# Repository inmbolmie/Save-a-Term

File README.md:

# Save-a-Term

Hardware for an IBM 5251 and 3278 reverse keyboard adapter to use a regular PS/2 keyboard with the original terminals. Based on my TMK controller fork (https://github.com/inmbolmie/ps2_to_4704_converter)

## Introduction

You got a pretty vintage 5251 or 3278 terminal but it lacks the original keyboard. The original keyboards are very expensive and sought-after items that can easily go for thousands of dollars. This adapter tries to solve that problem giving a way to use a cheap standard PS/2-like keyboard with the original terminals.

The adapter emulates the clicker functionality of the original keyboards using a buzzer to give audible feedback while typing.

The adapter will also auto-detect the terminal type (5251 or 3278) and use the correct scancode set and signal polarities for the connected terminal.

If you like it, want an adapter or PCB, or need any information not covered here you can drop me an email to the address:  inmbolmie [AT] gmail [DOT] com

## Compatibility

This converter is only compatible with original IBM 5251 and 3278 terminals.

- The original IBM 5251 terminal keyboard has a DB25 female connector
- The original IBM 3278 terminal keyboard has a DB25 male connector

If not totally sure, check the voltages accross your terminal connector pins before plugging it to the adapter, here you have the expected 5251 and 3278 keyboard pinouts:

__This adapter is not compatible with other similar IBM connectors like 3277, 5291 or Displaywriter, so do not try it with those.__

This is not an adapter to plug an original 5251/3278 keyboard to a modern PC and won't ever work like that, so don't ask.

Pinouts are fully incompatible so a different connector is provided for each terminal type. Moreover, __it is dangerous to connect the terminal to the wrong connector as pretty weird voltages will be misplaced accross the connector (+8.5V, +5V, -5V) so you can fry the converter and/or terminal doing that, so be warned.__

This controller do not pretend to be universal in the sense some keyboards could be not compatible, but to provide a reasonable selection of cheap keyboards readily available. I have tested the converter using:

* Regular IBM model M
* IBM PC (XT)
* IBM AT (Model F)
* IBM terminal keyboards (M and F)
* Several PS/2 compatible keyboards

As said, it is not guaranteed that a particular keyboard will work, but there is a more than reasonable chance that any keyboard compatible with those metioned will work.

This converter is NOT compatible with USB keyboards. The pro-micro USB connector is provided only as way to update the controller's firmware.

## Usage

The adapter will get power from the terminal connector, so no external power is needed.

For the connection to the terminal you have to use a __male-to-female straight DB-25 cable__

To use the adapter you simply have to plug __ONE keyboard__ to one of the 4 available ports (RJ45, DIN5-240º, DIN5-180º, PS/2) and __the terminal to the right DB-25 connector (female for 5251 and male for 3278)__. The terminal type and connector gender is also clearly marked on the PCB silkscreen. Check that your cable is really straight, pin 1 goes to pin 1, pin 2 goes to pin 2, etc. __It is of the utmost importance not to mix genders or plug the terminal to the wrong connector__, as pretty high voltages are involved on the connectors (+8.5V, +5V. -5V) and the pinouts are incompatible. If you get it wrong you will damage the adapted and/or terminal. __You cannot get it wrong if you stick to only using a male-to-female straight DB25 cable__, as there is no way of plugging it on a wrong configuration.

The adapter will auto-detect the terminal type (5251 or 3278) and use the correct scancode set and signal polarities for the connected terminal.

The buzzer volume can be adjusted using the on-board potentiometer. On the spririt of the original keyboards, the buzzer can be totally silenced only from the terminal (like the clicker on the original keyboards).

The included DIP switches allow to configure a 4-bit keyboard-id for the terminal. The keyboard-id is exclusively used by the terminal and do not modify the adapter operation.

## Layouts

The layouts are designed to replicate the original keyboard functionality. They are not configurable.

### 5251 using a codeset 1 keyboard (XT)

This is the recommended layout for 5251, as it is exactly the same as the original keyboard

### 5251 using a codeset 2 or 3 keyboard (AT/PS2/Terminal)

Offers the same functionality as the original keyboard, placing keys on similar positions.

### 3278 using a codeset 2 or 3 keyboard (AT/PS2/Terminal)

This is the recommended layout for 3278, offers extra fuctionality and layout loosely based on 122-key 3270-compatible terminals

### 3278 using a codeset 1 keyboard (XT)

Do not use it as some keys will be on weird places, offered only for compatibility reasons.

## Kicad files

### Schematics

The design is based on the pro-micro version of TMK adding parallel protocol compatibility.

### PCB

## Case

I provide the STL files for a 3D-printed case (case and lid). The case is assembled using 4 M3x10mm tapered head screws.

## Fabrication

You can order the PCB's directly from JLCPCB using the provided gerber, bom, and cpl files on the `pcb` directory. You can easily generate files for other fabricators from the Kicad project files.

## Assembly

For the assembly be sure you get the correct gender for DB-25 connectors respecting what is indicated on the silkscreen legends.

You have to use a 5V-16Mhz Arduino pro-micro genuine or compatible microcontroller.

The 7805 regulator can be a regular 7805 or (better) a DC-to-DC pin compatible replacement like a Traco TSR 1-2450E. A 7805 is used to power the board from the 8.5V rail instead of using the +5V rail directly because I found the latter unstable and sometimes providing insufficient voltage to power the controller reliably.

## Programming

You have to use my fork of TMK https://github.com/inmbolmie/ps2_to_4704_converter

`git clone https://github.com/inmbolmie/ps2_to_4704_converter.git`

Go to the `converter/ibmpc_ibm5251` directory and generate the firmware file executing:

`cd ps2_to_4704_converter/converter/ibmpc_ibm5251/`

`make -f Makefile.atmega32u4`

To program the controller, connect it to an USB port on your computer, making sure no terminal is connected to the adapter in case the controller is already soldered on the board. Then push the RESET button on the board and execute on your computer:

`avrdude -p m32U4 -P /dev/ttyACM0 -c avr109 -U flash:w:ibmpc_ibm5251_atmega32u4.hex`

 Where `ibmpc_ibm5251_atmega32u4.hex` is the name of the generated firmware file.

The device name `ttyACM0` could have to be changed to whatever device name your computer assigns to your controller.

__Do not plug the USB port while a terminal is connected to the adapter__

You will need to have the tools needed to build TMK, follow the general instrucions from the TMK code to configure your build environment.

After successful programming you will get output like this:

    Connecting to programmer: .
    Found programmer: Id = "CATERIN"; type = S
        Software Version = 1.0; No Hardware Version given.
    Programmer supports auto addr increment.
    Programmer supports buffered memory access with buffersize=128 bytes.

    Programmer supports the following devices:
        Device code: 0x44

    avrdude: AVR device initialized and ready to accept instructions

    Reading | ################################################## | 100% 0.00s

    avrdude: Device signature = 0x1e9587 (probably m32u4)
    avrdude: NOTE: "flash" memory has been specified, an erase cycle will be performed
             To disable this feature, specify the -D option.
    avrdude: erasing chip
    avrdude: reading input file "ibmpc_ibm5251_atmega32u4.hex"
    avrdude: input file ibmpc_ibm5251_atmega32u4.hex auto detected as Intel Hex
    avrdude: writing flash (27136 bytes):

    Writing | ################################################## | 100% 1.69s

    avrdude: 27136 bytes of flash written
    avrdude: verifying flash memory against ibmpc_ibm5251_atmega32u4.hex:
    avrdude: load data flash data from input file ibmpc_ibm5251_atmega32u4.hex:
    avrdude: input file ibmpc_ibm5251_atmega32u4.hex auto detected as Intel Hex
    avrdude: input file ibmpc_ibm5251_atmega32u4.hex contains 27136 bytes
    avrdude: reading on-chip flash data:

    Reading | ################################################## | 100% 0.17s

    avrdude: verifying ...
    avrdude: 27136 bytes of flash verified

    avrdude: safemode: Fuses OK (E:CB, H:D8, L:FF)

    avrdude done.  Thank you.

Now your controller is ready to be used.

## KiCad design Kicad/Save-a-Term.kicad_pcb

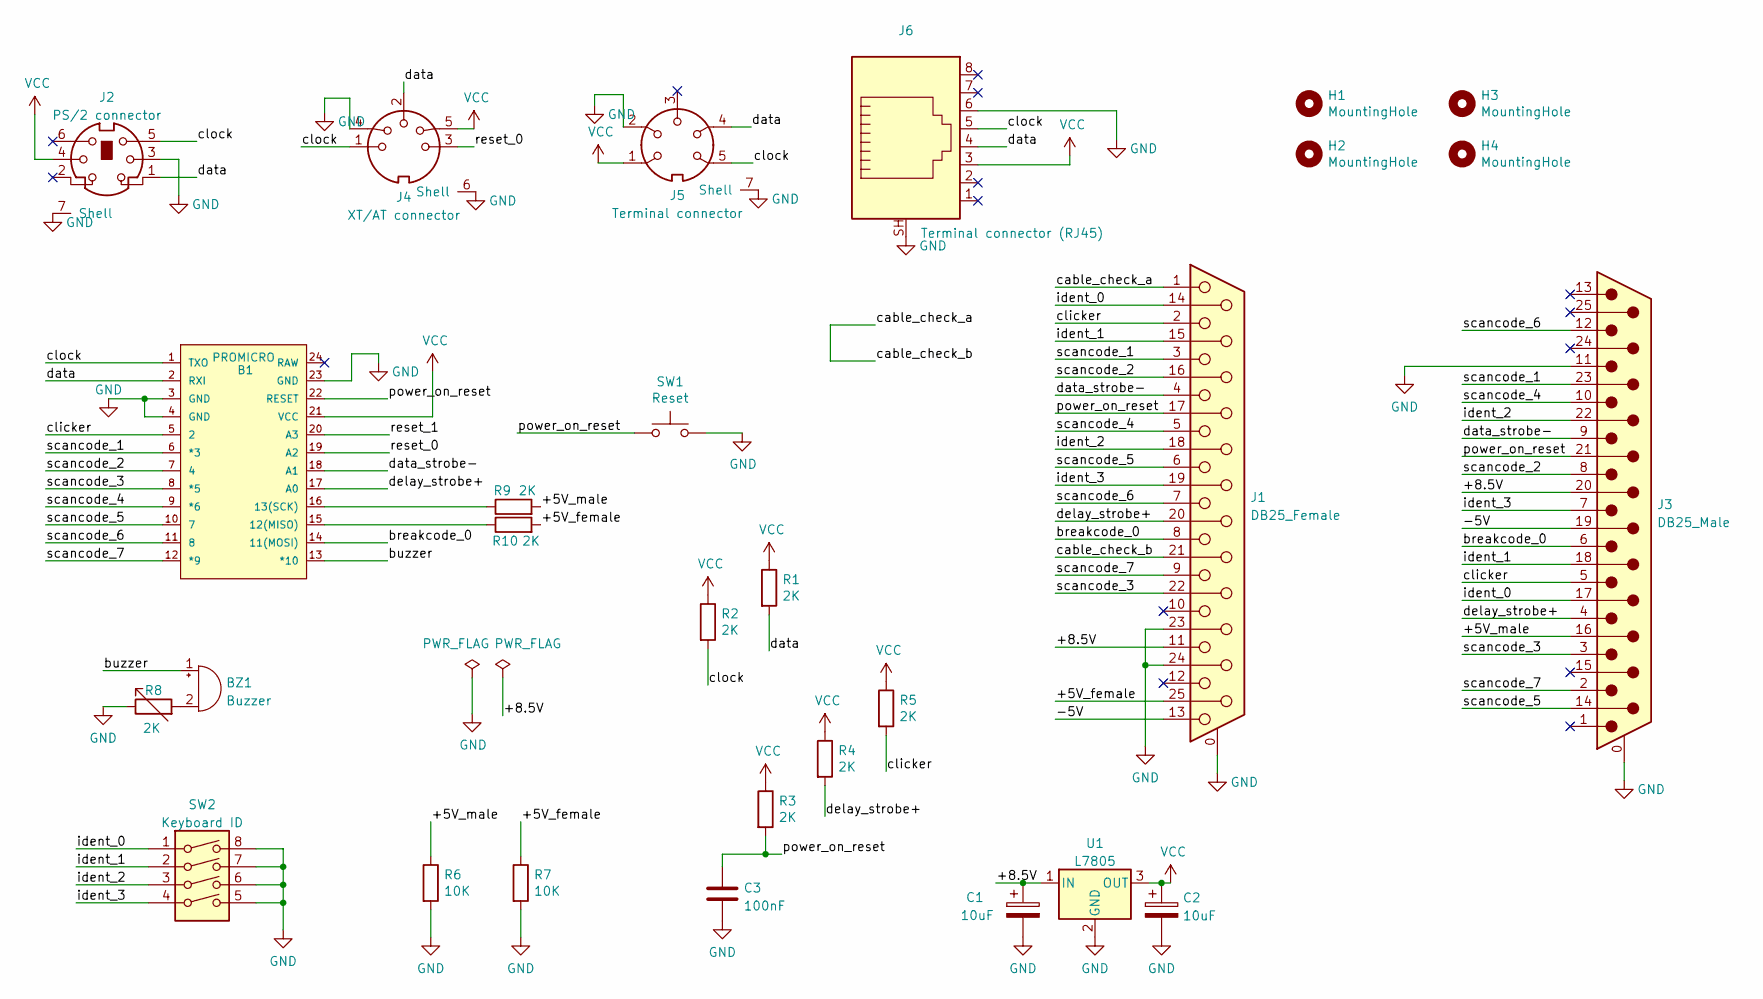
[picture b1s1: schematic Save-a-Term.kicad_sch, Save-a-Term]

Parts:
B1: PROMICRO; SPARKFUN_PRO_MICRO
BZ1: Buzzer; Buzzer_12x9.5RM7.6
C1, C2: 10uF; C_1206_3216Metric; LCSC C13585
C3: 100nF; C_0603_1608Metric; LCSC C14663
H1, H2, H3, H4: MountingHole; MountingHole_3.2mm_M3
J1: DB25_Female; DSUB-25_Female_Horizontal_P2.77x2.84mm_EdgePinOffset7.70mm_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
J2: PS/2 connector; Connector_Mini-DIN_Female_6Pin_2rows
J3: DB25_Male; DSUB-25_Male_Horizontal_P2.77x2.84mm_EdgePinOffset7.70mm_Ho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
J4: XT/AT connector; DIN-5
J5: Terminal connector; DIN-6
J6: Terminal connector (RJ45); RJ45_Ninigi_GE
R1, R2, R3, R4, R5, R9, R10: 2K; R_0603_1608Metric; LCSC C269690
R6, R7: 10K; R_0603_1608Metric; LCSC C25804
R8: 2K; RES-ADJ-SMD_G43BT; LCSC C128144
SW1: Reset; SW_Push_1P1T_NO_6x6mm_H9.5mm; LCSC C221880
SW2: Keyboard ID; Dip SW lateral 4; LCSC C319050
U1: L7805; TO-220-3_Vertical

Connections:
/+5V_female: J1.25, R7.1, R10.2
/+5V_male: J3.16, R6.1, R9.2
/+8.5V: C1.1, J1.11, J3.20, U1.1 (IN)
/-5V: J1.13, J3.19
/breakcode_0: B1.14 (11(MOSI)), J1.8, J3.6
/buzzer: B1.13 (*10), BZ1.1 (-)
/cable_check_a: J1.1, J1.21
/clicker: B1.5 (2), J1.2, J3.5, R5.2
/clock: B1.1 (TXO), J2.5, J4.1, J5.5, J6.5, R2.2
/data: B1.2 (RXI), J2.1, J4.2, J5.4, J6.4, R1.2
/data_strobe-: B1.18 (A1), J1.4, J3.9
/delay_strobe+: B1.17 (A0), J1.20, J3.4, R4.2
/ident_0: J1.14, J3.17, SW2.1
/ident_1: J1.15, J3.18, SW2.2
/ident_2: J1.18, J3.22, SW2.3
/ident_3: J1.19, J3.7, SW2.4
/power_on_reset: B1.22 (RESET), C3.1, J1.17, J3.21, R3.2, SW1.1
/reset_0: B1.19 (A2), J4.3
/reset_1: B1.20 (A3)
/scancode_1: B1.6 (*3), J1.3, J3.23
/scancode_2: B1.7 (4), J1.16, J3.8
/scancode_3: B1.8 (*5), J1.22, J3.3
/scancode_4: B1.9 (*6), J1.5, J3.10
/scancode_5: B1.10 (7), J1.6, J3.14
/scancode_6: B1.11 (8), J1.7, J3.12
/scancode_7: B1.12 (*9), J1.9, J3.2
GND: B1.3 (GND), B1.4 (GND), B1.23 (GND), C1.2, C2.2, C3.2, J1.0 (PAD), J1.23, J1.24, J2.3, J2.7 (Shell), J3.0 (PAD), J3.11, J4.4, J4.6 (Shell), J5.2, J5.7 (Shell), J6.6, J6.SH, R6.2, R7.2, R8.1, SW1.2, SW2.5, SW2.6, SW2.7, SW2.8, U1.2 (GND)
unnamed: B1.15 (12(MISO)), R10.1
unnamed: B1.16 (13(SCK)), R9.1
unnamed: BZ1.2 (+), R8.2
VCC: B1.21 (VCC), C2.1, J2.4, J4.5, J5.1, J6.3, R1.1, R2.1, R3.1, R4.1, R5.1, U1.3 (OUT)

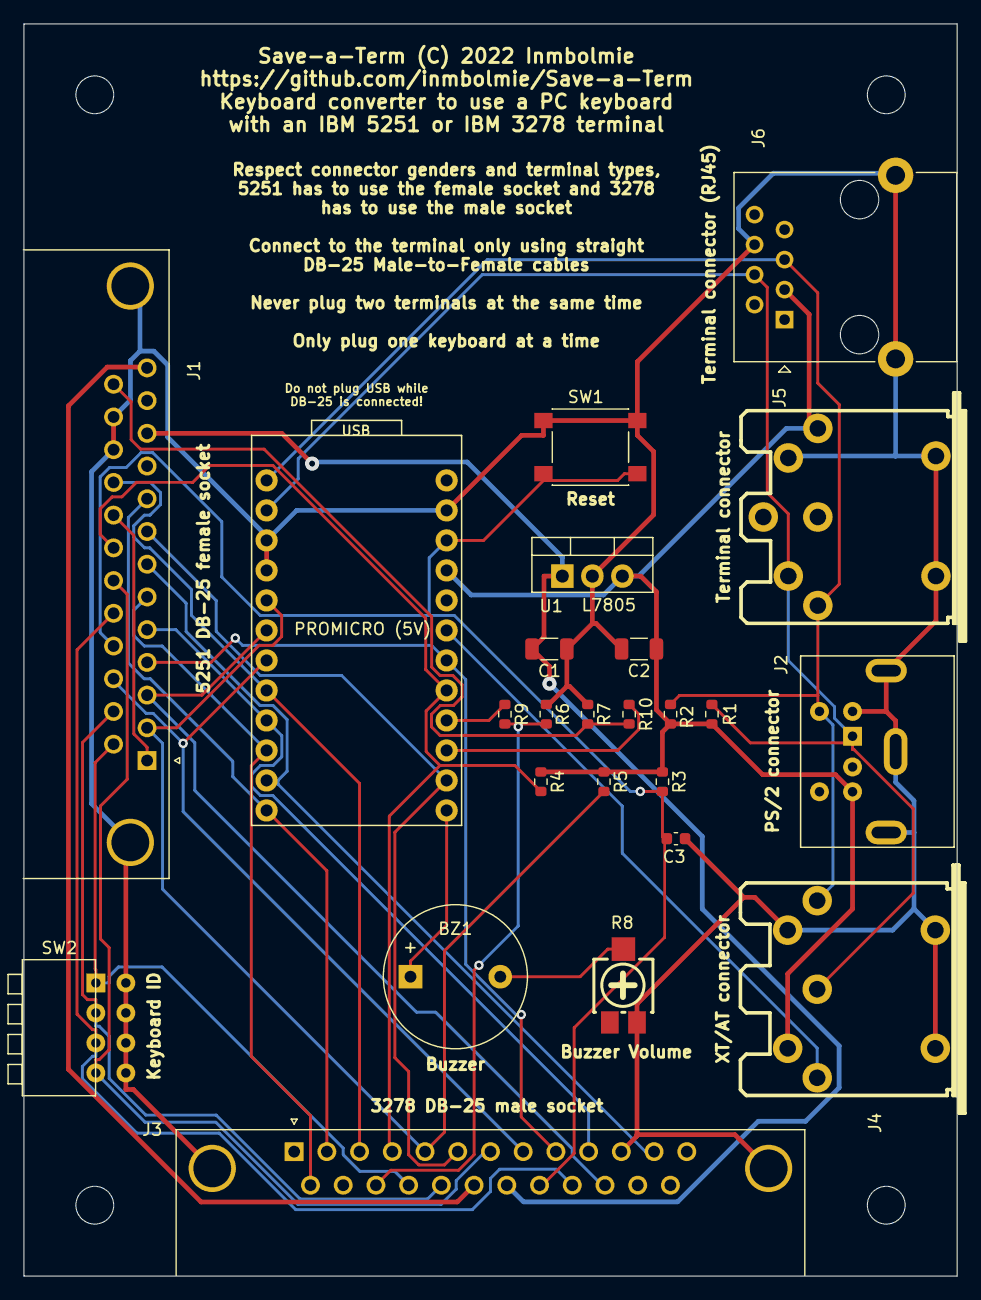
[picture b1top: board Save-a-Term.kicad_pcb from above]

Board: 2 copper layers, 79.0 x 106.0 mm, 28 parts (0 on the bottom side), 30 nets.

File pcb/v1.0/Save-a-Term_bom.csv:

Comment,Designator,Footprint,LCSC
10uF,"C1,C2",Capacitor_SMD:C_1206_3216Metric,C13585
100nF,C3,Capacitor_SMD:C_0603_1608Metric,C14663
2K,"R1,R2,R3,R4,R5,R9,R10",Resistor_SMD:R_0603_1608Metric,C269690
10K,"R6,R7",Resistor_SMD:R_0603_1608Metric,C25804
2K,R8,mis_partes:RES-ADJ-SMD_G43BT,C128144
Reset,SW1,Button_Switch_SMD:SW_Push_1P1T_NO_6x6mm_H9.5mm,C221880

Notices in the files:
Kicad/Save-a-Term.kicad_pcb:
Save-a-Term (C) 2022 Inmbolmie
